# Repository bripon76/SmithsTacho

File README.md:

# SmithsTacho
DIY conversation from mechanical tachometer (RPM gauge) to electical one

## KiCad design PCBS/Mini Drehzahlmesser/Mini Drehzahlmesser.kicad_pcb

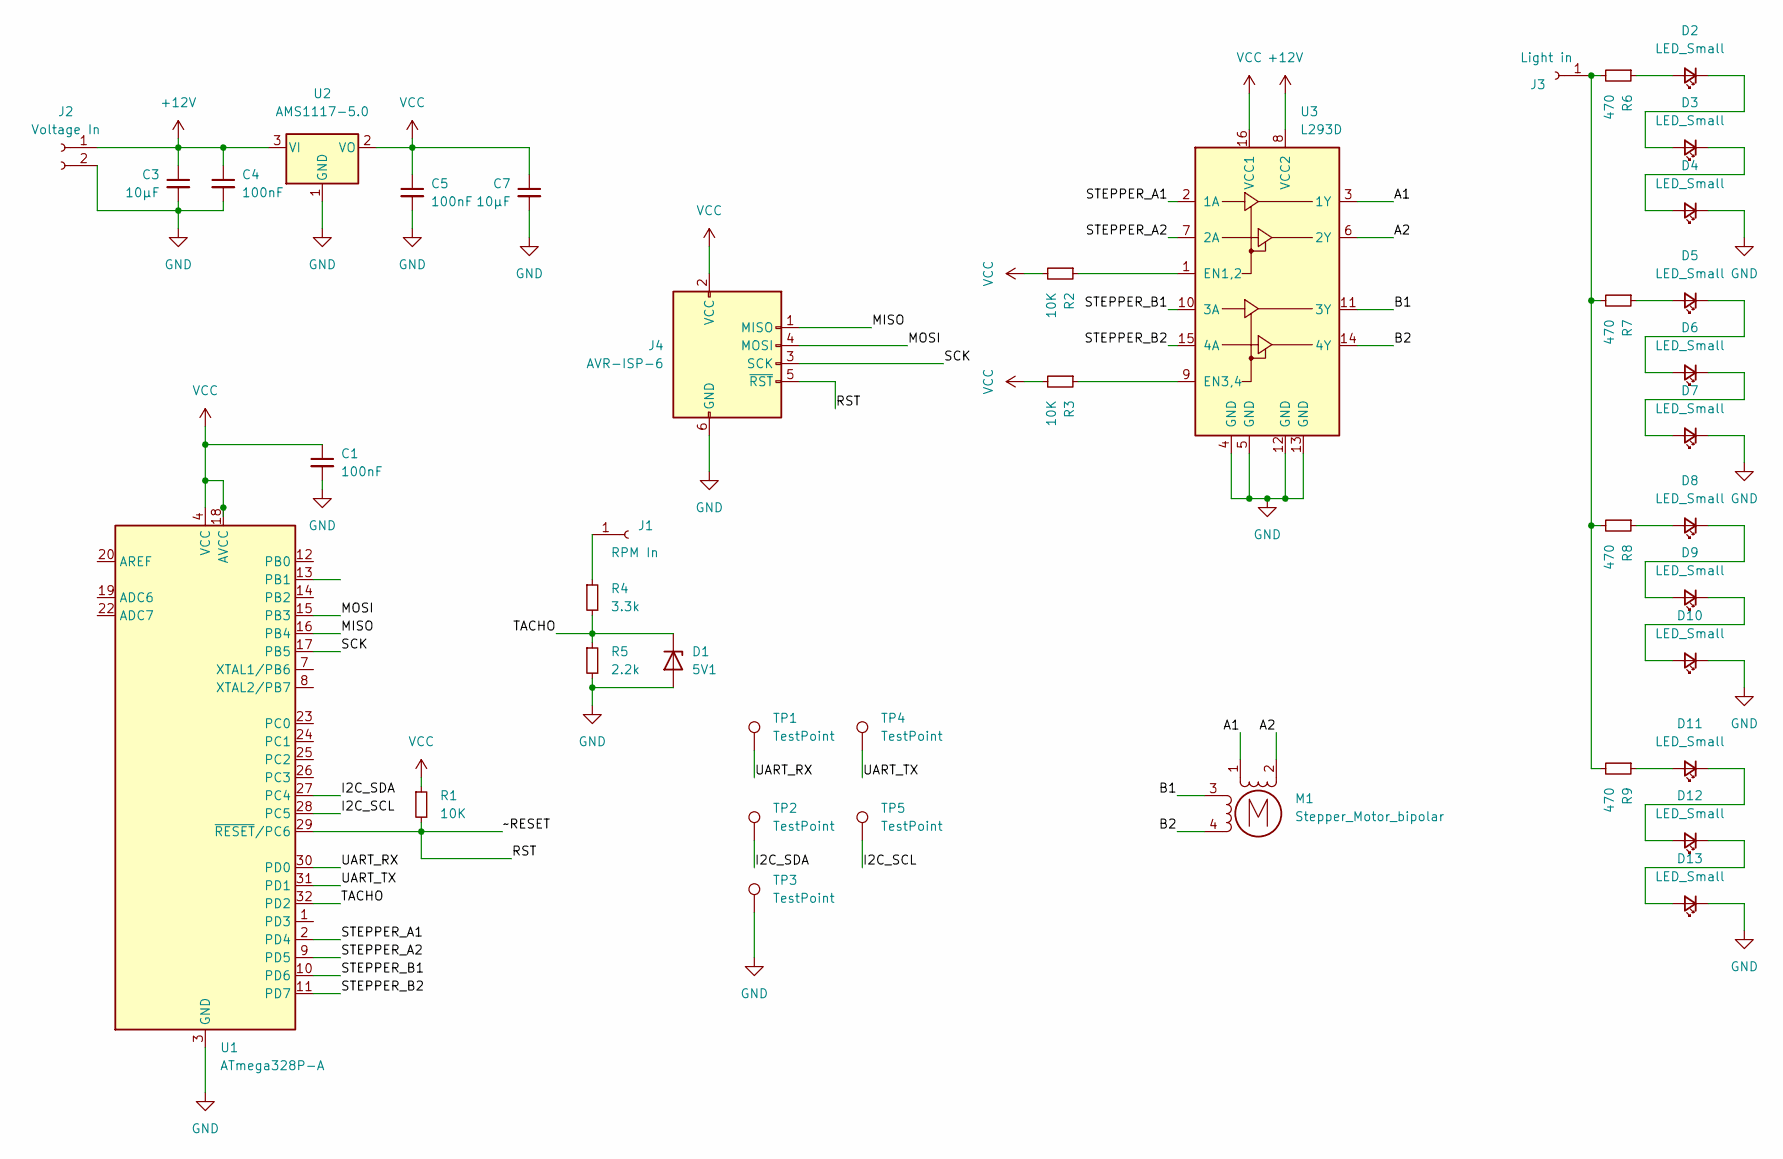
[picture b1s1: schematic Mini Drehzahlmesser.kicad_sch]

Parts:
C1, C4, C5: 100nF; C_0603_1608Metric_Pad1.08x0.95mm_HandSolder
C3, C7: 10µF; C_0805_2012Metric_Pad1.18x1.45mm_HandSolder
D1: 5V1; D_SOD-123
D2, D3, D4, D5, D6, D7, D8, D9, D10, D11, D12, D13: LED_Small; LED_1206_3216Metric_Pad1.42x1.75mm_HandSolder
J1: RPM In; SolderWire-0.5sqmm_1x01_D0.9mm_OD2.3mm
J2: Voltage In; SolderWire-0.5sqmm_1x02_P4.8mm_D0.9mm_OD2.3mm
J3: Light in; SolderWire-0.5sqmm_1x01_D0.9mm_OD2.3mm
J4: AVR-ISP-6; PinHeader_2x03_P2.54mm_Vertical
M1: Stepper_Motor_bipolar; X27-168
R1, R2, R3: 10K; R_0603_1608Metric_Pad0.98x0.95mm_HandSolder
R4: 3.3k; R_0603_1608Metric_Pad0.98x0.95mm_HandSolder
R5: 2.2k; R_0603_1608Metric_Pad0.98x0.95mm_HandSolder
R6, R7, R8, R9: 470; R_0603_1608Metric_Pad0.98x0.95mm_HandSolder
TP1, TP2, TP3, TP4, TP5: TestPoint; TestPoint_Pad_D2.0mm
U1: ATmega328P-A; TQFP-32_7x7mm_P0.8mm
U2: AMS1117-5.0; SOT-223-3_TabPin2
U3: L293D; DIP-16_W7.62mm

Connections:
+12V: C3.1, C4.1, J2.1, U2.3 (VI), U3.8 (VCC2)
/A1: M1.1, U3.3 (1Y)
/A2: M1.2 (-), U3.6 (2Y)
/B1: M1.3, U3.11 (3Y)
/B2: M1.4, U3.14 (4Y)
/I2C_SCL: TP5.1, U1.28 (PC5)
/I2C_SDA: TP2.1, U1.27 (PC4)
/MISO: J4.1 (MISO), U1.16 (PB4)
/MOSI: J4.4 (MOSI), U1.15 (PB3)
/RST: J4.5 (~RST), R1.2, U1.29 (~RESET/PC6)
/SCK: J4.3 (SCK), U1.17 (PB5)
/STEPPER_A1: U1.2 (PD4), U3.2 (1A)
/STEPPER_A2: U1.9 (PD5), U3.7 (2A)
/STEPPER_B1: U1.10 (PD6), U3.10 (3A)
/STEPPER_B2: U1.11 (PD7), U3.15 (4A)
/TACHO: D1.1 (K), R4.2, R5.1, U1.32 (PD2)
/UART_RX: TP1.1, U1.30 (PD0)
/UART_TX: TP4.1, U1.31 (PD1)
GND: C1.2, C3.2, C4.2, C5.2, C7.2, D1.2 (A), D4.1 (K), D7.1 (K), D10.1 (K), D13.1 (K), J2.2, J4.6 (GND), R5.2, TP3.1, U1.3 (GND), U1.5 (GND), U1.21 (GND), U2.1 (GND), U3.4 (GND), U3.5 (GND), U3.12 (GND), U3.13 (GND)
unnamed: D2.1 (K), D3.2 (A)
unnamed: D2.2 (A), R6.1
unnamed: D3.1 (K), D4.2 (A)
unnamed: D5.1 (K), D6.2 (A)
unnamed: D5.2 (A), R7.1
unnamed: D6.1 (K), D7.2 (A)
unnamed: D8.1 (K), D9.2 (A)
unnamed: D8.2 (A), R8.1
unnamed: D9.1 (K), D10.2 (A)
unnamed: D11.1 (K), D12.2 (A)
unnamed: D11.2 (A), R9.1
unnamed: D12.1 (K), D13.2 (A)
unnamed: J1.1, R4.1
unnamed: J3.1, R6.2, R7.2, R8.2, R9.2
unnamed: R2.1, U3.1 (EN1,2)
unnamed: R3.1, U3.9 (EN3,4)
VCC: C1.1, C5.1, C7.1, J4.2 (VCC), R1.1, R2.2, R3.2, U1.4 (VCC), U1.6 (VCC), U1.18 (AVCC), U2.2 (VO), U3.16 (VCC1)

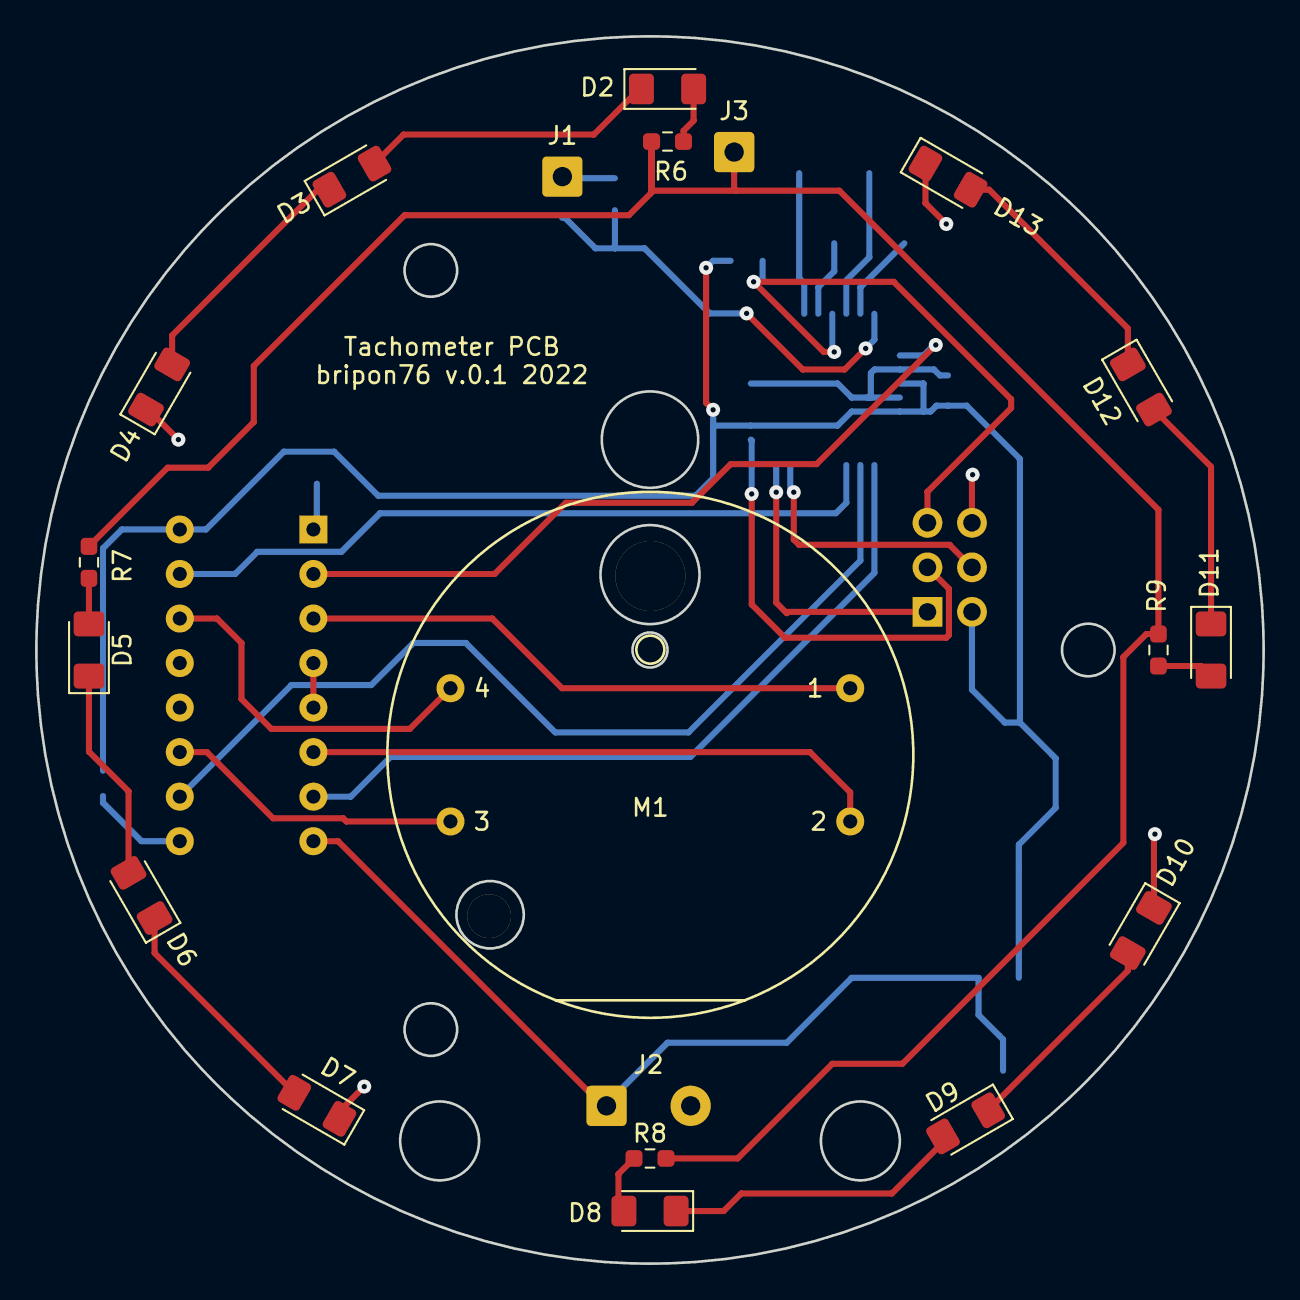
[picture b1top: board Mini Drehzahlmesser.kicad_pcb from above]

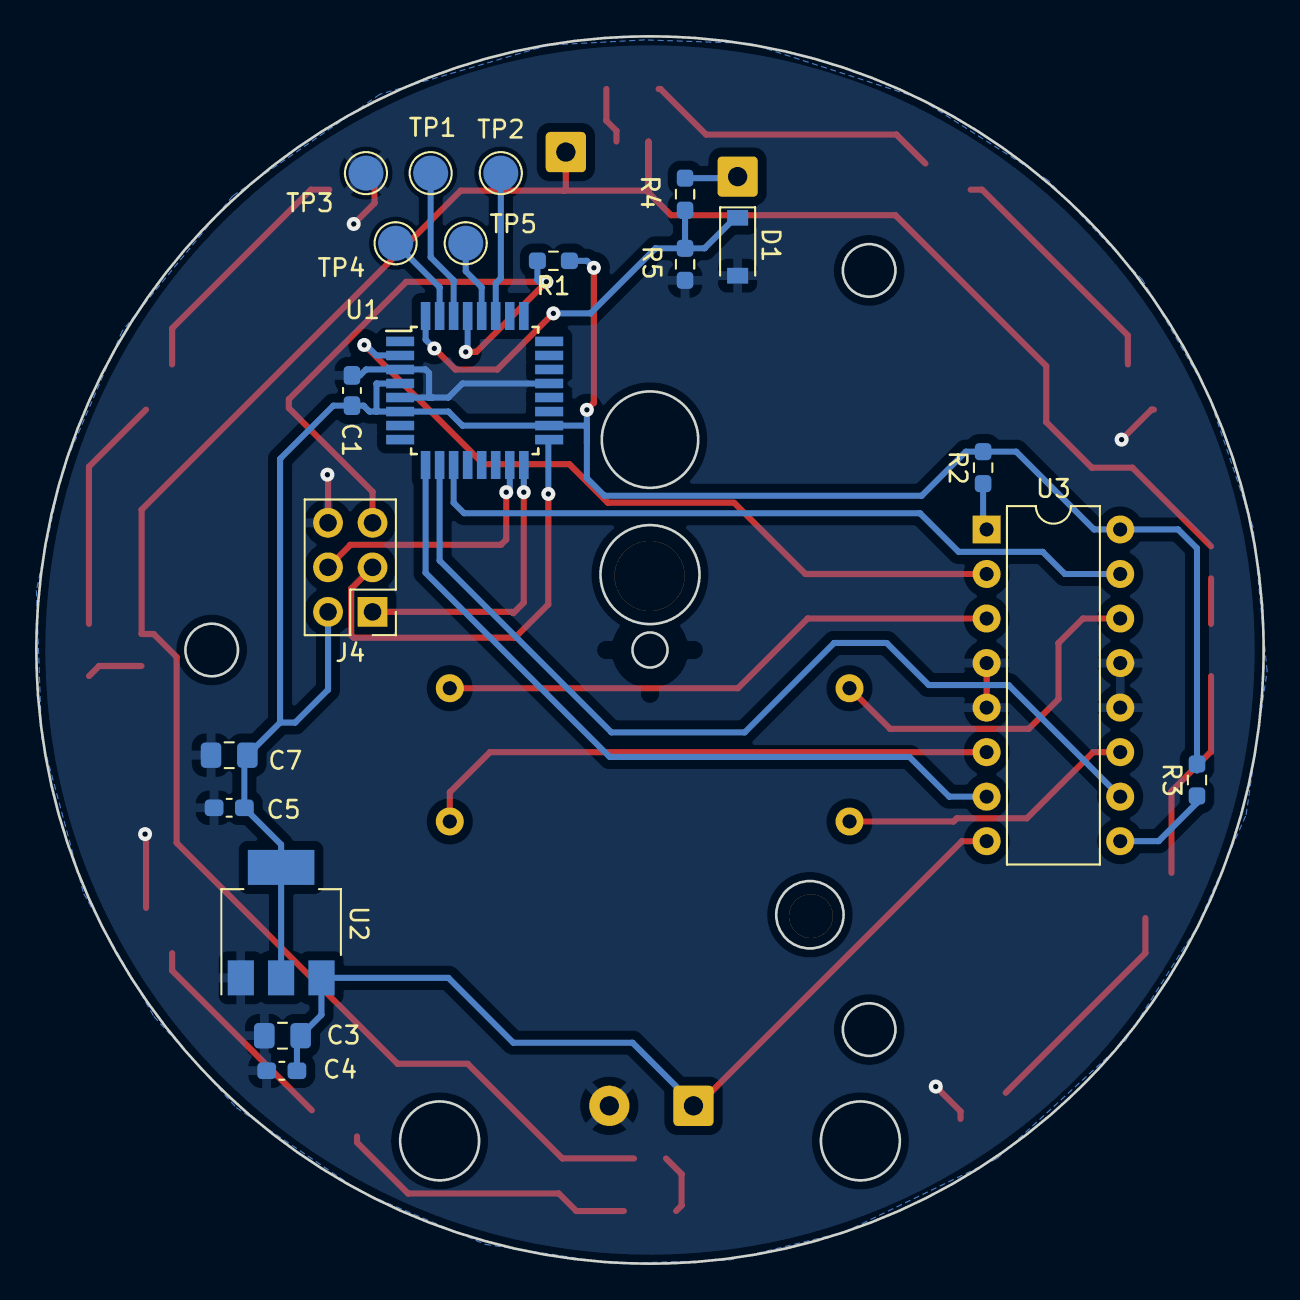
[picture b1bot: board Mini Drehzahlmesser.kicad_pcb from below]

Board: 2 copper layers, 70.0 x 70.0 mm, 40 parts (20 on the bottom side), 36 nets.

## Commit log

2023-01-14 Smiths Tacho mod mechanical to electical
